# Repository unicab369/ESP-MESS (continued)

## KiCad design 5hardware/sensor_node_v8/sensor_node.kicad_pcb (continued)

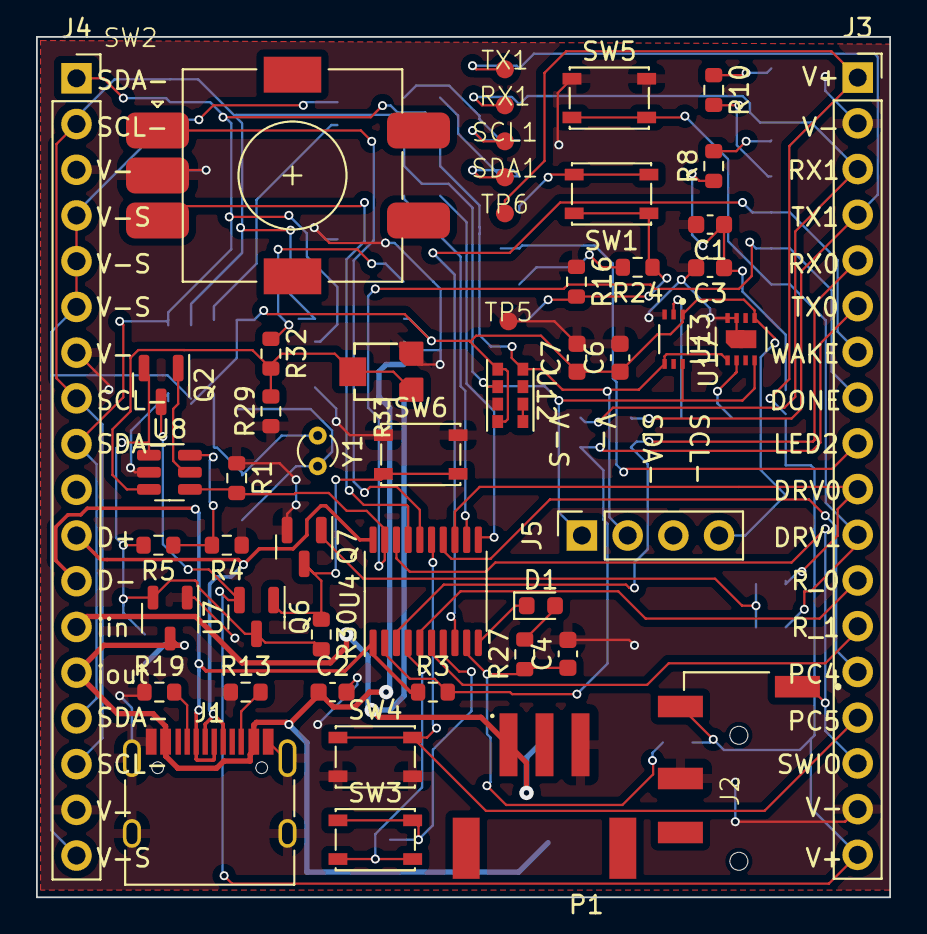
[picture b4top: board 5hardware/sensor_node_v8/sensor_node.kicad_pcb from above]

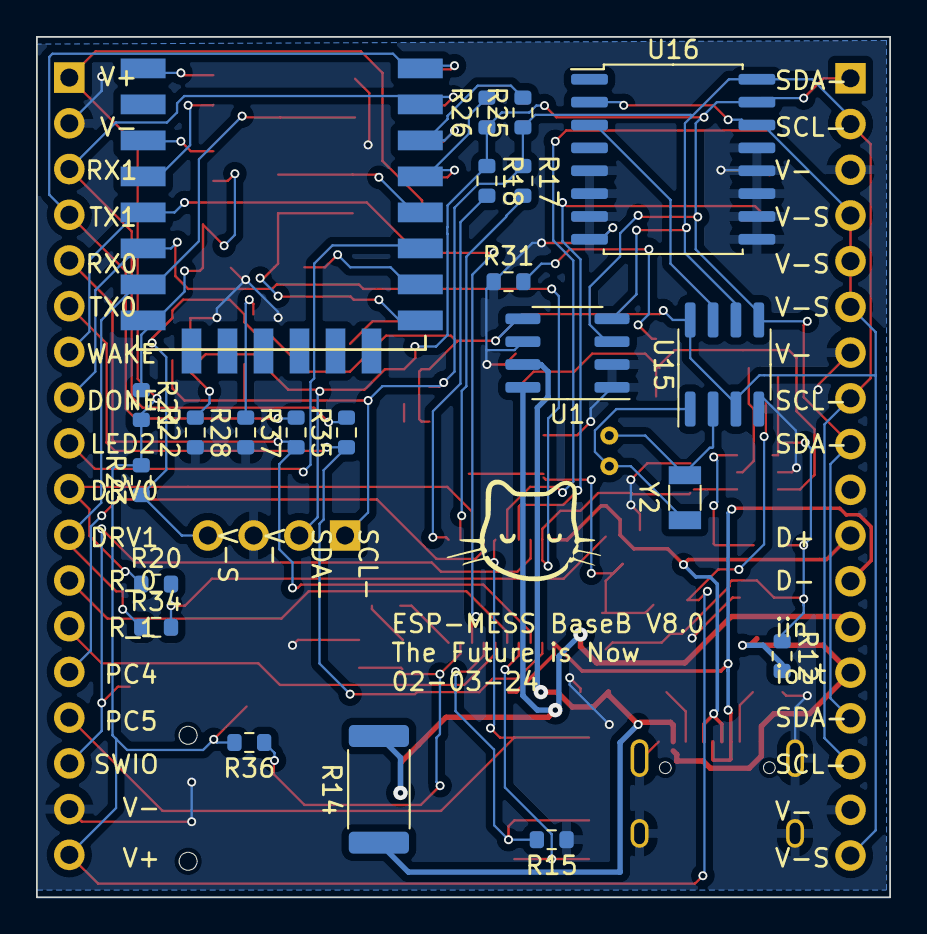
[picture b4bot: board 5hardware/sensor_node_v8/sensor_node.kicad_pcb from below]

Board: 2 copper layers, 47.4 x 47.8 mm, 72 parts (22 on the bottom side), 56 nets.
